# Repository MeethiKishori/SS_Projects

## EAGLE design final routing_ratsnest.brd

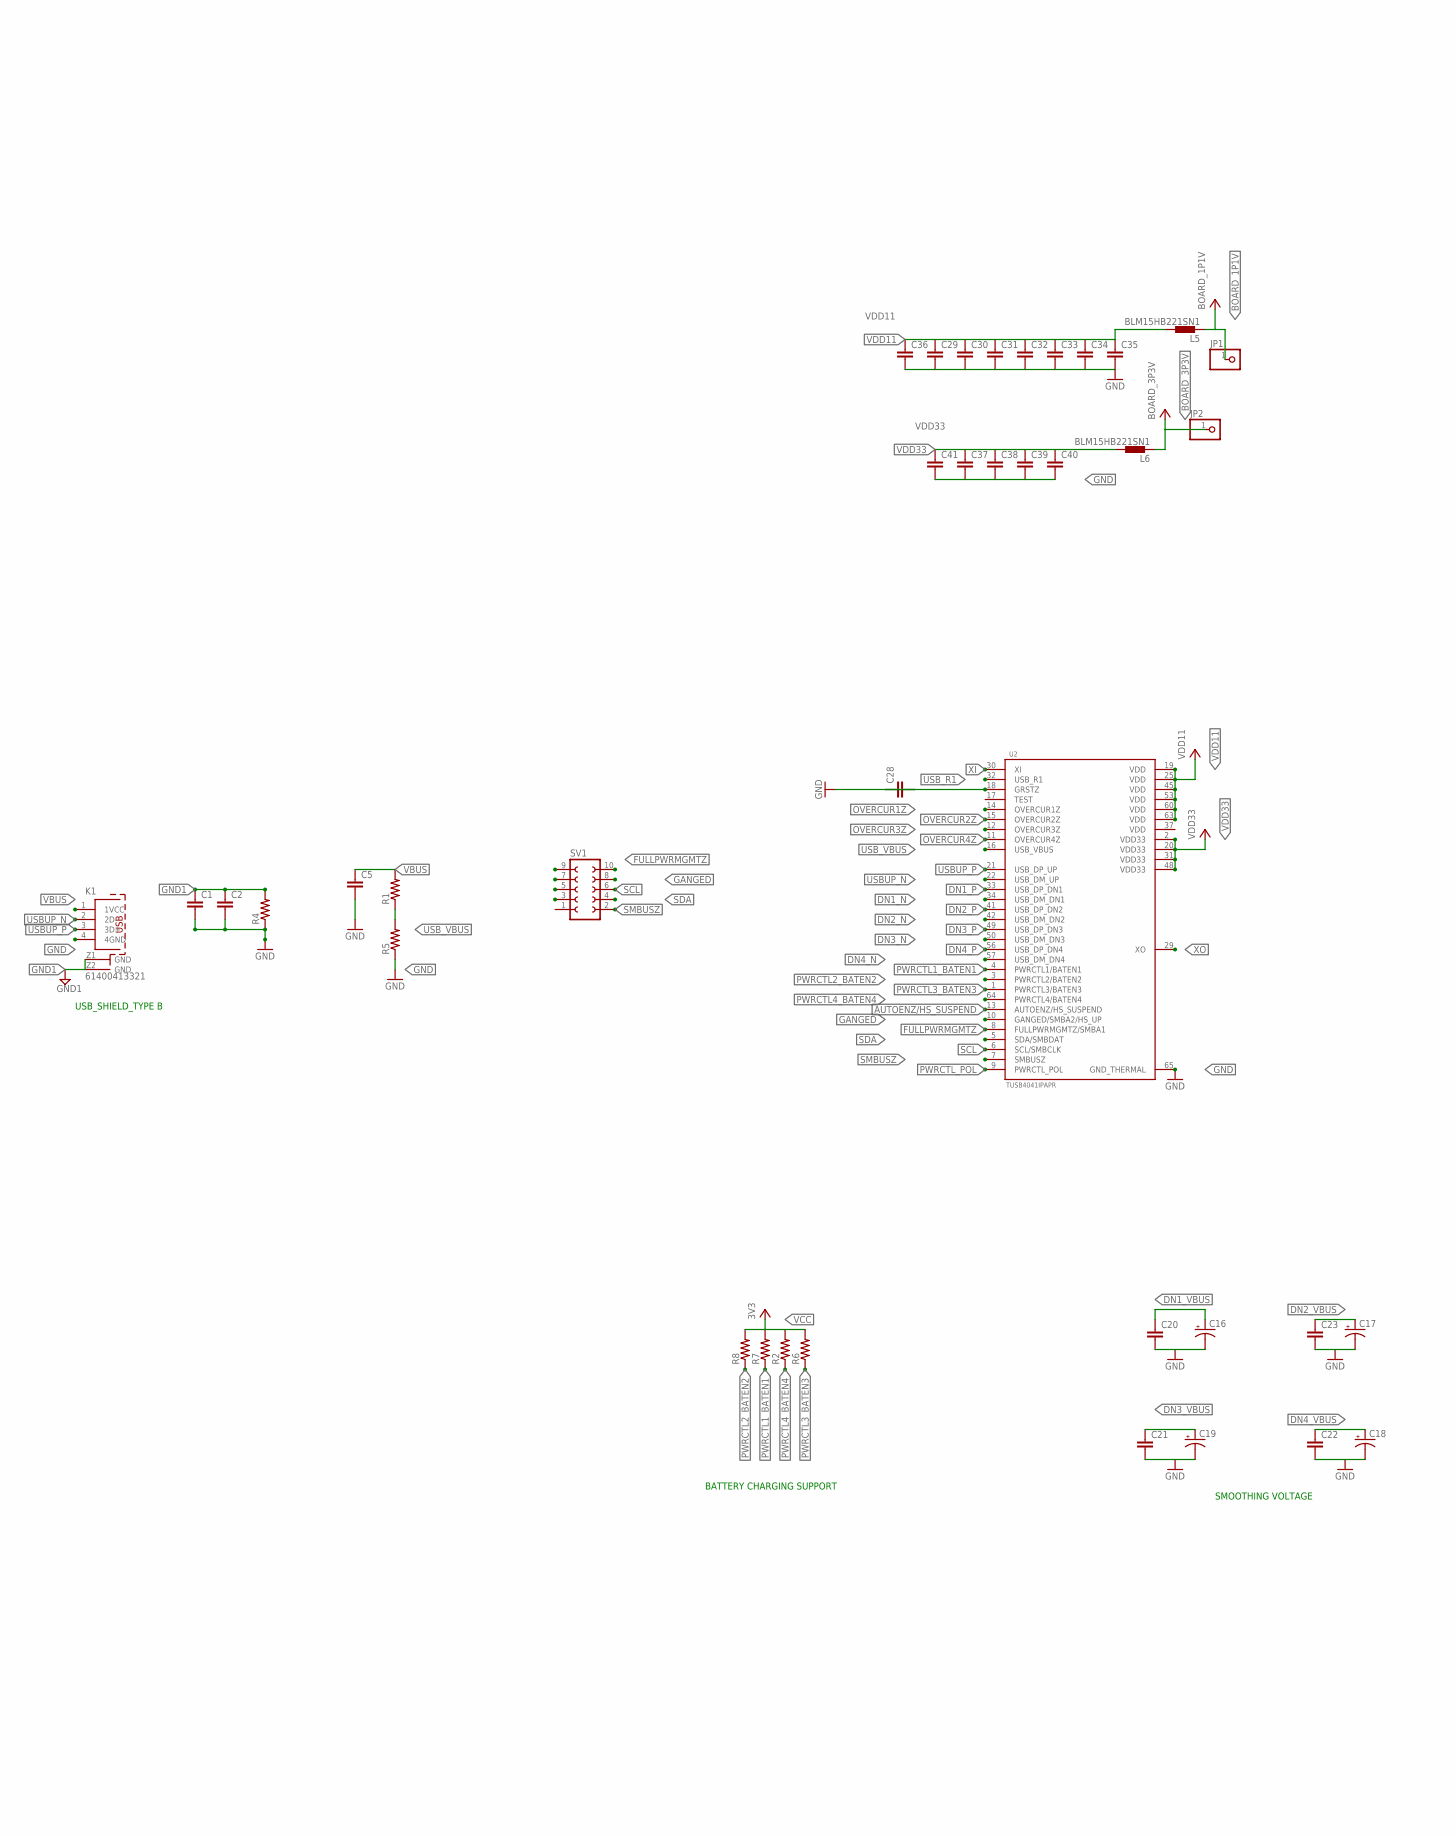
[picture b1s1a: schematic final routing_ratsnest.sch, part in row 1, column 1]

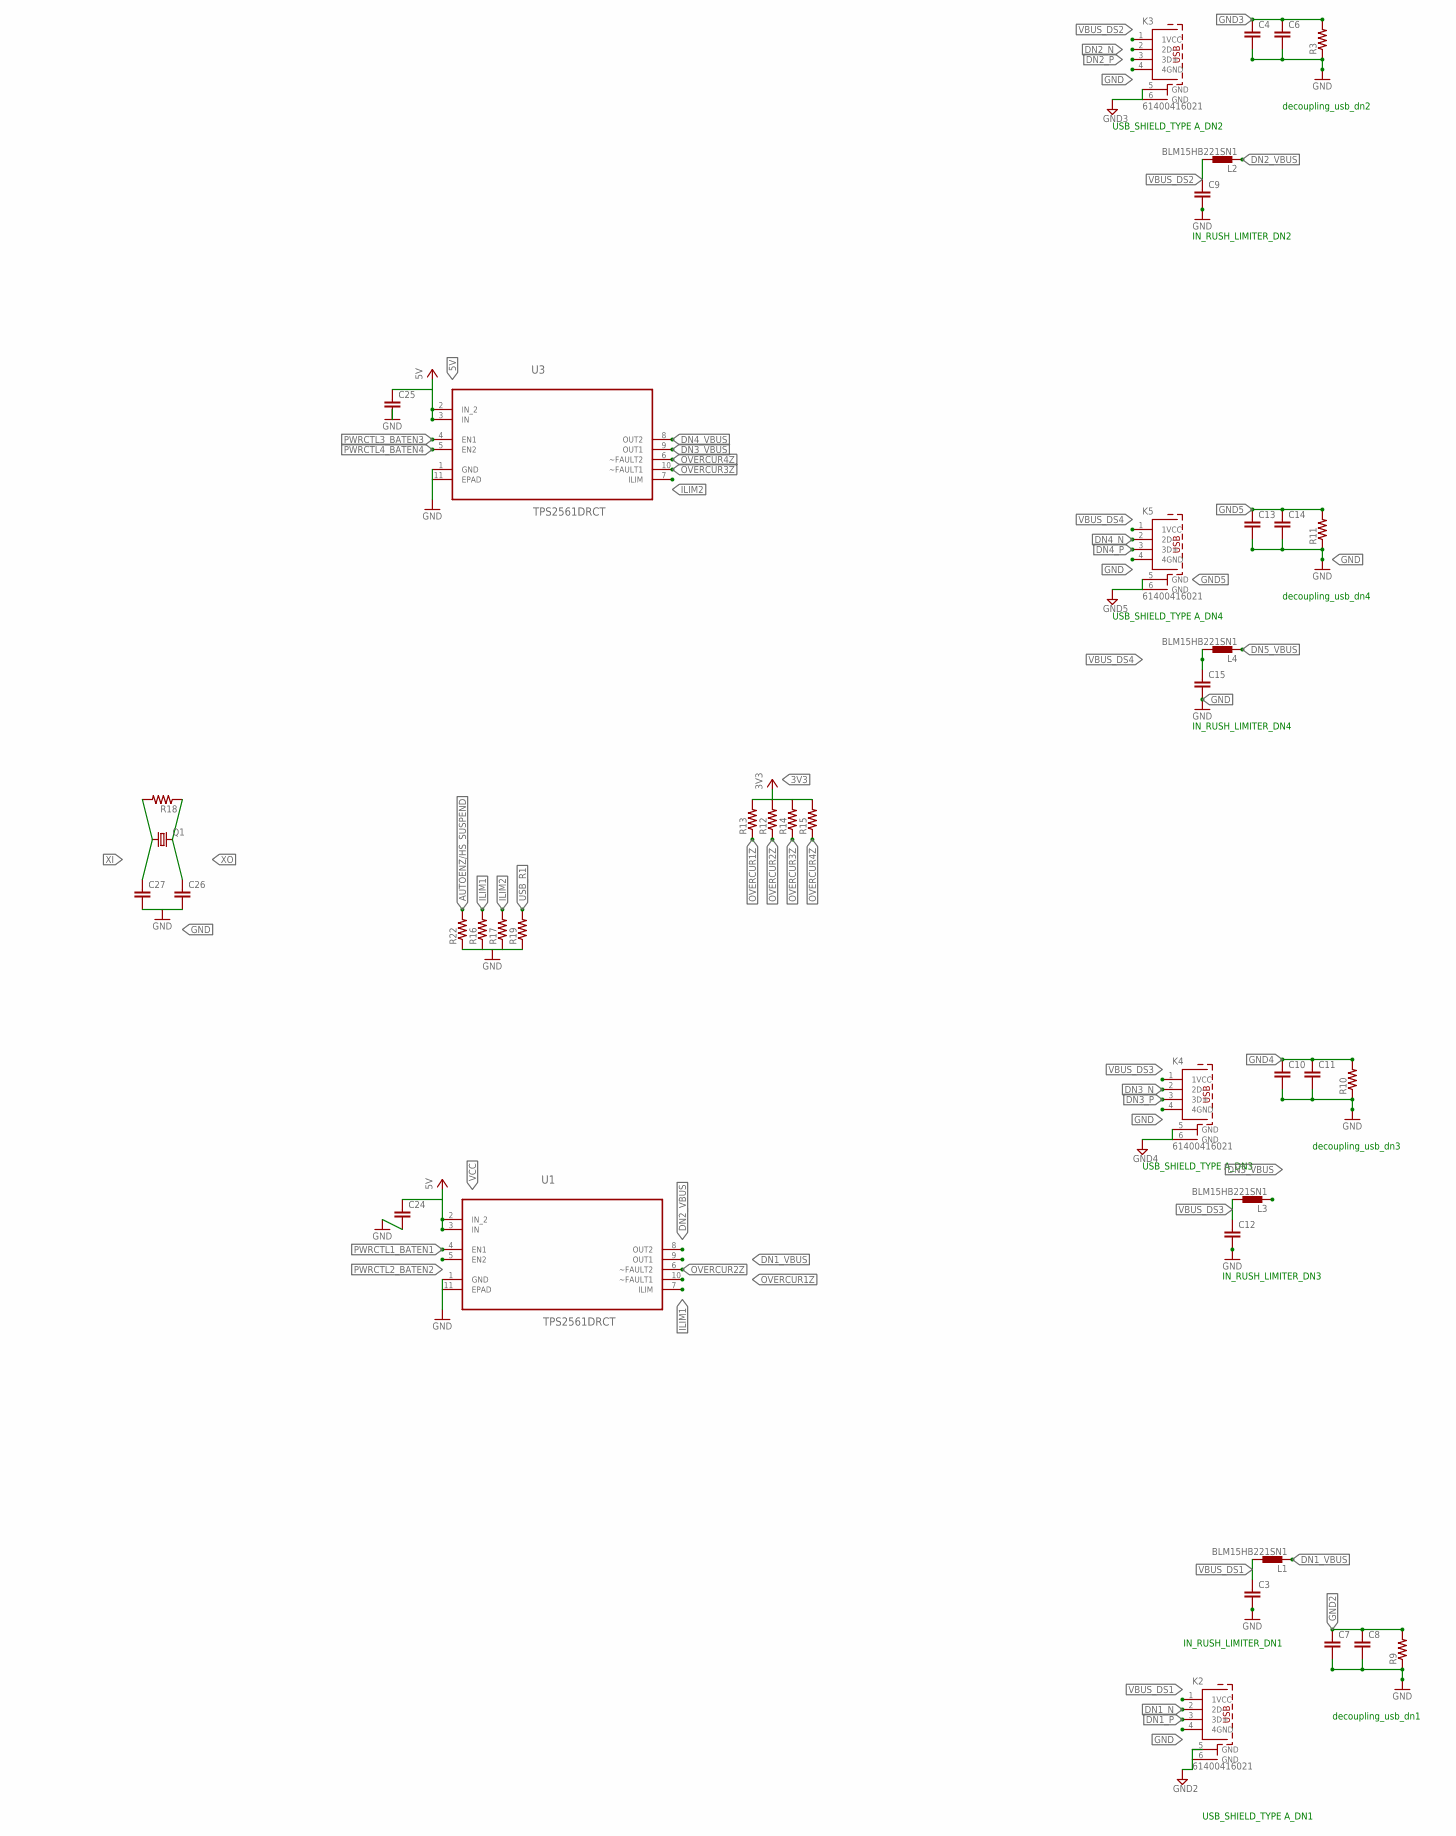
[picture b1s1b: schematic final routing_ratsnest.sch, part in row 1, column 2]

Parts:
C1, C2, C3, C4, C5, C6, C7, C8, C9, C10, C11, C12, C13, C14, C15: C2.5/4; C2.5-4
C16, C17, C18, C19: CPOL-USE5-5; E5-5
C20, C21, C22, C23, C24, C25, C26, C27, C28, C29, C30, C31, C32, C33, C34, C35, C36, C37, C38, C39, C40, C41: C2.5/2; C2.5-2
JP1, JP2: PINHD-1X1; 1X01
K1: 61400413321
K2, K3, K4, K5: 61400416021
L1, L2, L3, L4, L5, L6: BLM15HB221SN1; 0402
Q1: CRYSTALHC49S; HC49/S
R1, R2, R3, R4, R5, R6, R7, R8, R9, R10, R11, R12, R13, R14, R15, R16, R17, R18, R19, R22: R-US_R2010W; R2010W
SV1: FE05-2
U1, U3: TPS2561DRCT; SON50P300X300X100-11N
U2: TUSB4041IPAPR; QFP50P1200X1200X105-65N

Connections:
3V3: R12.2, R13.2, R14.2, R15.2
5V: C25.1, U3.2 (IN_2), U3.3 (IN)
AUTOENZ/HS_SUSPEND: R22.2, U2.13 (AUTOENZ/HS_SUSPEND)
BOARD_1P1V: JP1.1, L5.1
BOARD_3P3V: JP2.1, L6.1
DN1_N: K2.2 (2D-), U2.34 (USB_DM_DN1)
DN1_P: K2.3 (3D+), U2.33 (USB_DP_DN1)
DN1_VBUS: C16.+, C20.1, L1.1, U1.9 (OUT1)
DN2_N: K3.2 (2D-), U2.42 (USB_DM_DN2)
DN2_P: K3.3 (3D+), U2.41 (USB_DP_DN2)
DN2_VBUS: C17.+, C23.1, L2.1, U1.8 (OUT2)
DN3_N: K4.2 (2D-), U2.50 (USB_DM_DN3)
DN3_P: K4.3 (3D+), U2.49 (USB_DP_DN3)
DN3_VBUS: C19.+, C21.1, L3.1, U3.9 (OUT1)
DN4_N: K5.2 (2D-), U2.57 (USB_DM_DN4)
DN4_P: K5.3 (3D+), U2.56 (USB_DP_DN4)
DN4_VBUS: C18.+, C22.1, U3.8 (OUT2)
DN5_VBUS: L4.1
FULLPWRMGMTZ: SV1.10, U2.8 (FULLPWRMGMTZ/SMBA1)
GANGED: SV1.8, U2.10 (GANGED/SMBA2/HS_UP)
GND: C1.2, C2.2, C3.2, C4.2, C5.2, C6.2, C7.2, C8.2, C9.2, C10.2, C11.2, C12.2, C13.2, C14.2, C15.2, C16.-, C17.-, C18.-, C19.-, C20.2, C21.2, C22.2, C23.2, C24.2, C25.2, C26.2, C27.2, C28.2, C29.2, C30.2, C31.2, C32.2, C33.2, C34.2, C35.2, C36.2, C37.2, C38.2, C39.2, C40.2, C41.2, K1.4 (4GND), K2.4 (4GND), K3.4 (4GND), K4.4 (4GND), K5.4 (4GND), R3.1, R4.1, R5.1, R9.1, R10.1, R11.1, R16.1, R17.1, R19.1, R22.1, U1.1 (GND), U1.11 (EPAD), U2.65 (GND_THERMAL), U3.1 (GND), U3.11 (EPAD)
GND1: C1.1, C2.1, K1.Z1 (GND), K1.Z2 (GND), R4.2
GND2: C7.1, C8.1, K2.5 (GND), K2.6 (GND), R9.2
GND3: C4.1, C6.1, K3.5 (GND), K3.6 (GND), R3.2
GND4: C10.1, C11.1, K4.5 (GND), K4.6 (GND), R10.2
GND5: C13.1, C14.1, K5.5 (GND), K5.6 (GND), R11.2
GRSTZ: C28.1, U2.18 (GRSTZ)
ILIM1: R16.2, U1.7 (ILIM)
ILIM2: R17.2, U3.7 (ILIM)
OVERCUR1Z: R13.1, U1.10 (~FAULT1), U2.14 (OVERCUR1Z)
OVERCUR2Z: R12.1, U1.6 (~FAULT2), U2.15 (OVERCUR2Z)
OVERCUR3Z: R14.1, U2.12 (OVERCUR3Z), U3.10 (~FAULT1)
OVERCUR4Z: R15.1, U2.11 (OVERCUR4Z), U3.6 (~FAULT2)
PWRCTL1_BATEN1: R7.1, U1.4 (EN1), U2.4 (PWRCTL1/BATEN1)
PWRCTL2_BATEN2: R8.1, U1.5 (EN2), U2.3 (PWRCTL2/BATEN2)
PWRCTL3_BATEN3: R6.1, U2.1 (PWRCTL3/BATEN3), U3.4 (EN1)
PWRCTL4_BATEN4: R2.1, U2.64 (PWRCTL4/BATEN4), U3.5 (EN2)
PWRCTL_POL: U2.9 (PWRCTL_POL)
SCL: SV1.6, U2.6 (SCL/SMBCLK)
SDA: SV1.4, U2.5 (SDA/SMBDAT)
SMBUSZ: SV1.2, U2.7 (SMBUSZ)
USBUP_N: K1.2 (2D-), U2.22 (USB_DM_UP)
USBUP_P: K1.3 (3D+), U2.21 (USB_DP_UP)
USB_R1: R19.2, U2.32 (USB_R1)
USB_VBUS: R1.1, R5.2, U2.16 (USB_VBUS)
VBUS: C5.1, K1.1 (1VCC), R1.2
VBUS_DS1: C3.1, K2.1 (1VCC), L1.2
VBUS_DS2: C9.1, K3.1 (1VCC), L2.2
VBUS_DS3: C12.1, K4.1 (1VCC), L3.2
VBUS_DS4: C15.1, K5.1 (1VCC), L4.2
VCC: C24.1, R2.2, R6.2, R7.2, R8.2, U1.2 (IN_2), U1.3 (IN)
VDD: U2.37 (VDD)
VDD11: C29.1, C30.1, C31.1, C32.1, C33.1, C34.1, C35.1, C36.1, L5.2, U2.19 (VDD), U2.25 (VDD), U2.45 (VDD), U2.53 (VDD), U2.60 (VDD), U2.63 (VDD)
VDD33: C37.1, C38.1, C39.1, C40.1, C41.1, L6.2, U2.2 (VDD33), U2.20 (VDD33), U2.31 (VDD33), U2.48 (VDD33)
XI: C27.1, Q1.1, R18.2, U2.30 (XI)
XO: C26.1, Q1.2, R18.1, U2.29 (XO)

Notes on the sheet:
USB_SHIELD_TYPE B
decoupling_usb_dn1
USB_SHIELD_TYPE A_DN1
USB_SHIELD_TYPE A_DN2
decoupling_usb_dn2
IN_RUSH_LIMITER_DN2
IN_RUSH_LIMITER_DN1
USB_SHIELD_TYPE A_DN3
decoupling_usb_dn3
IN_RUSH_LIMITER_DN3
USB_SHIELD_TYPE A_DN4
decoupling_usb_dn4
IN_RUSH_LIMITER_DN4
BATTERY CHARGING SUPPORT
SMOOTHING VOLTAGE

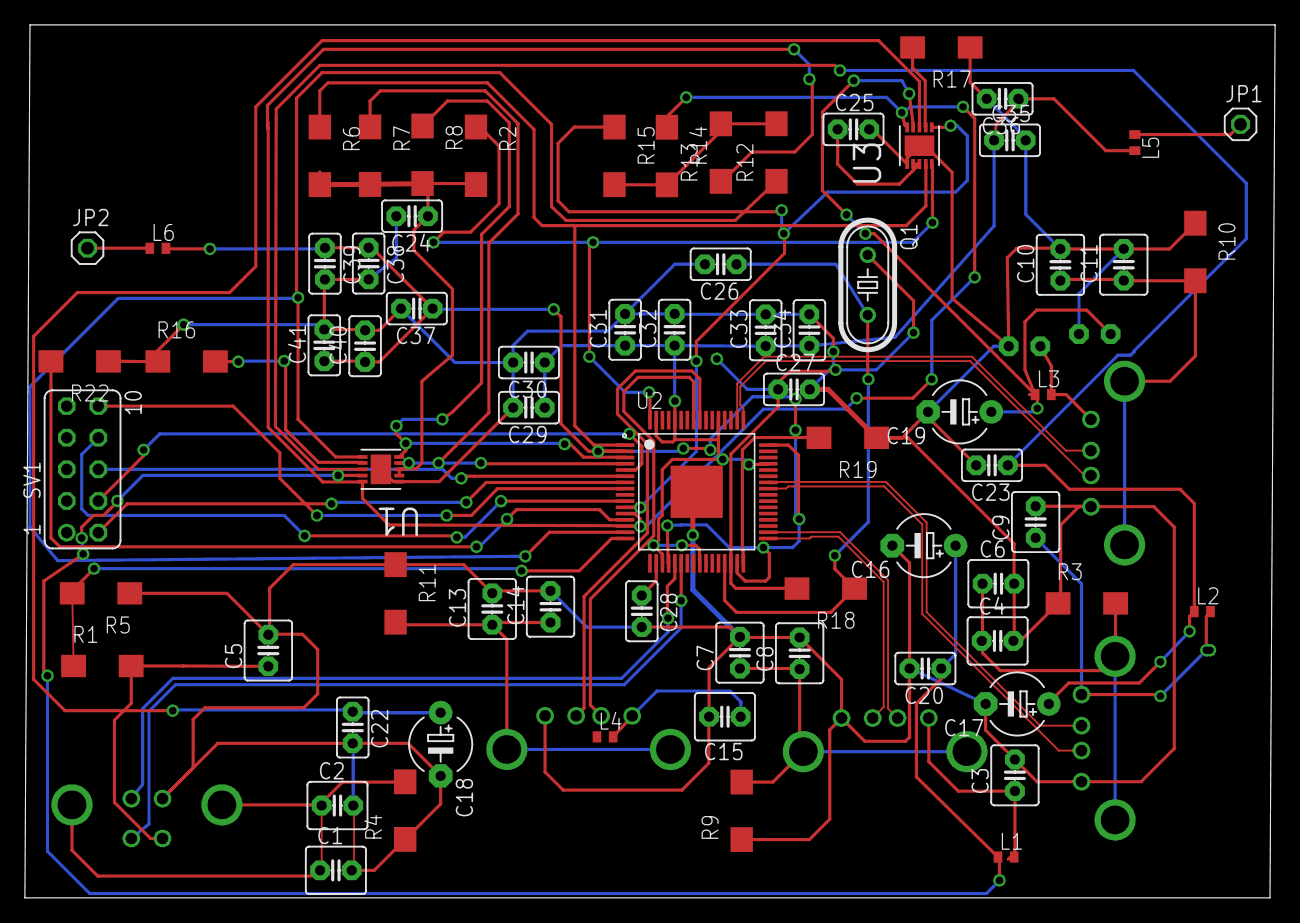
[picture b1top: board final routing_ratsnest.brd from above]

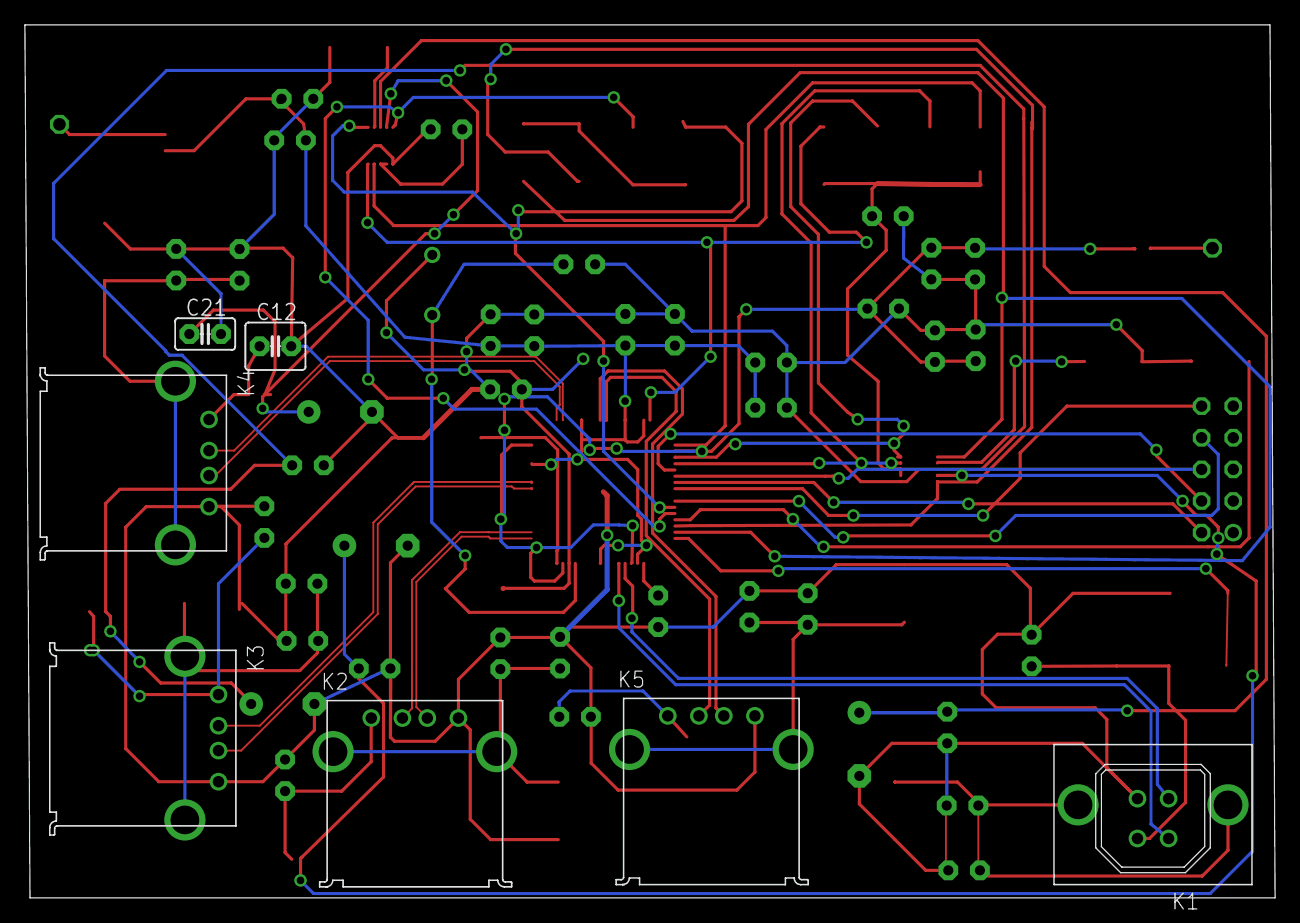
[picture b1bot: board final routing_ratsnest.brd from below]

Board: 2 copper layers, 100.4 x 70.1 mm, 79 parts (7 on the bottom side), 53 nets.

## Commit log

2025-06-18 usb hub controller
2025-06-18 USB hub controller board jpg
2025-06-18 .brd of the usb controller
2025-06-18 .sch file of the usb controller
2025-06-18 Phase shifted full bridge converter matlab file
2025-06-20 Autonomous Vehicle
2025-06-20 Portfolio
    It includes my experience and project i worked on in past.
    It always gets updated.
2025-06-20 RRLAB
    Images
2025-06-20 mini projects
    obstacle avoider and other
2025-06-20 Portfolio

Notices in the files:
parts and their libraries:
Wurth_Input-Output_Connectors_rev15d: Copyright: Würth Elektronik
